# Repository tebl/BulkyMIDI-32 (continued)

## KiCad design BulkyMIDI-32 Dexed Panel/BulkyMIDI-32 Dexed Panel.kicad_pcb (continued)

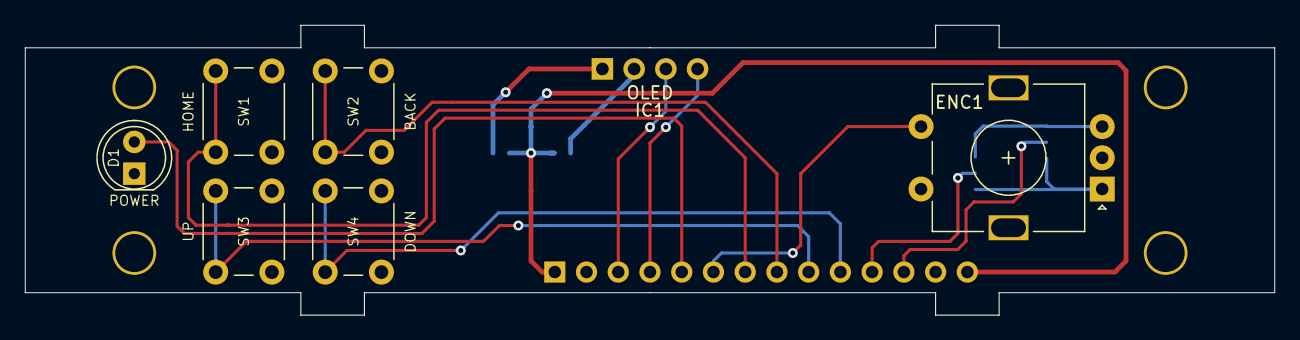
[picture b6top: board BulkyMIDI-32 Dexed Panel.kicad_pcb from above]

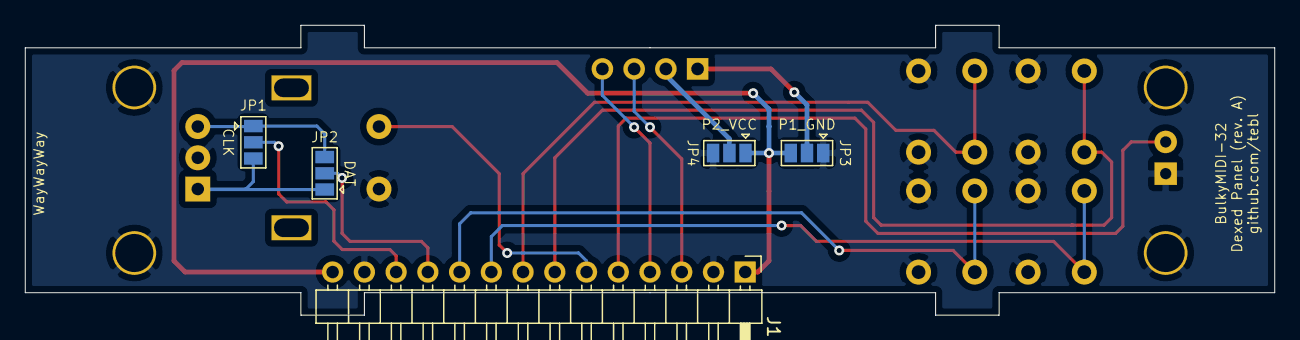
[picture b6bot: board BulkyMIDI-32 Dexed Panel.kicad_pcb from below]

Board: 2 copper layers, 100.0 x 23.2 mm, 16 parts (5 on the bottom side), 16 nets.

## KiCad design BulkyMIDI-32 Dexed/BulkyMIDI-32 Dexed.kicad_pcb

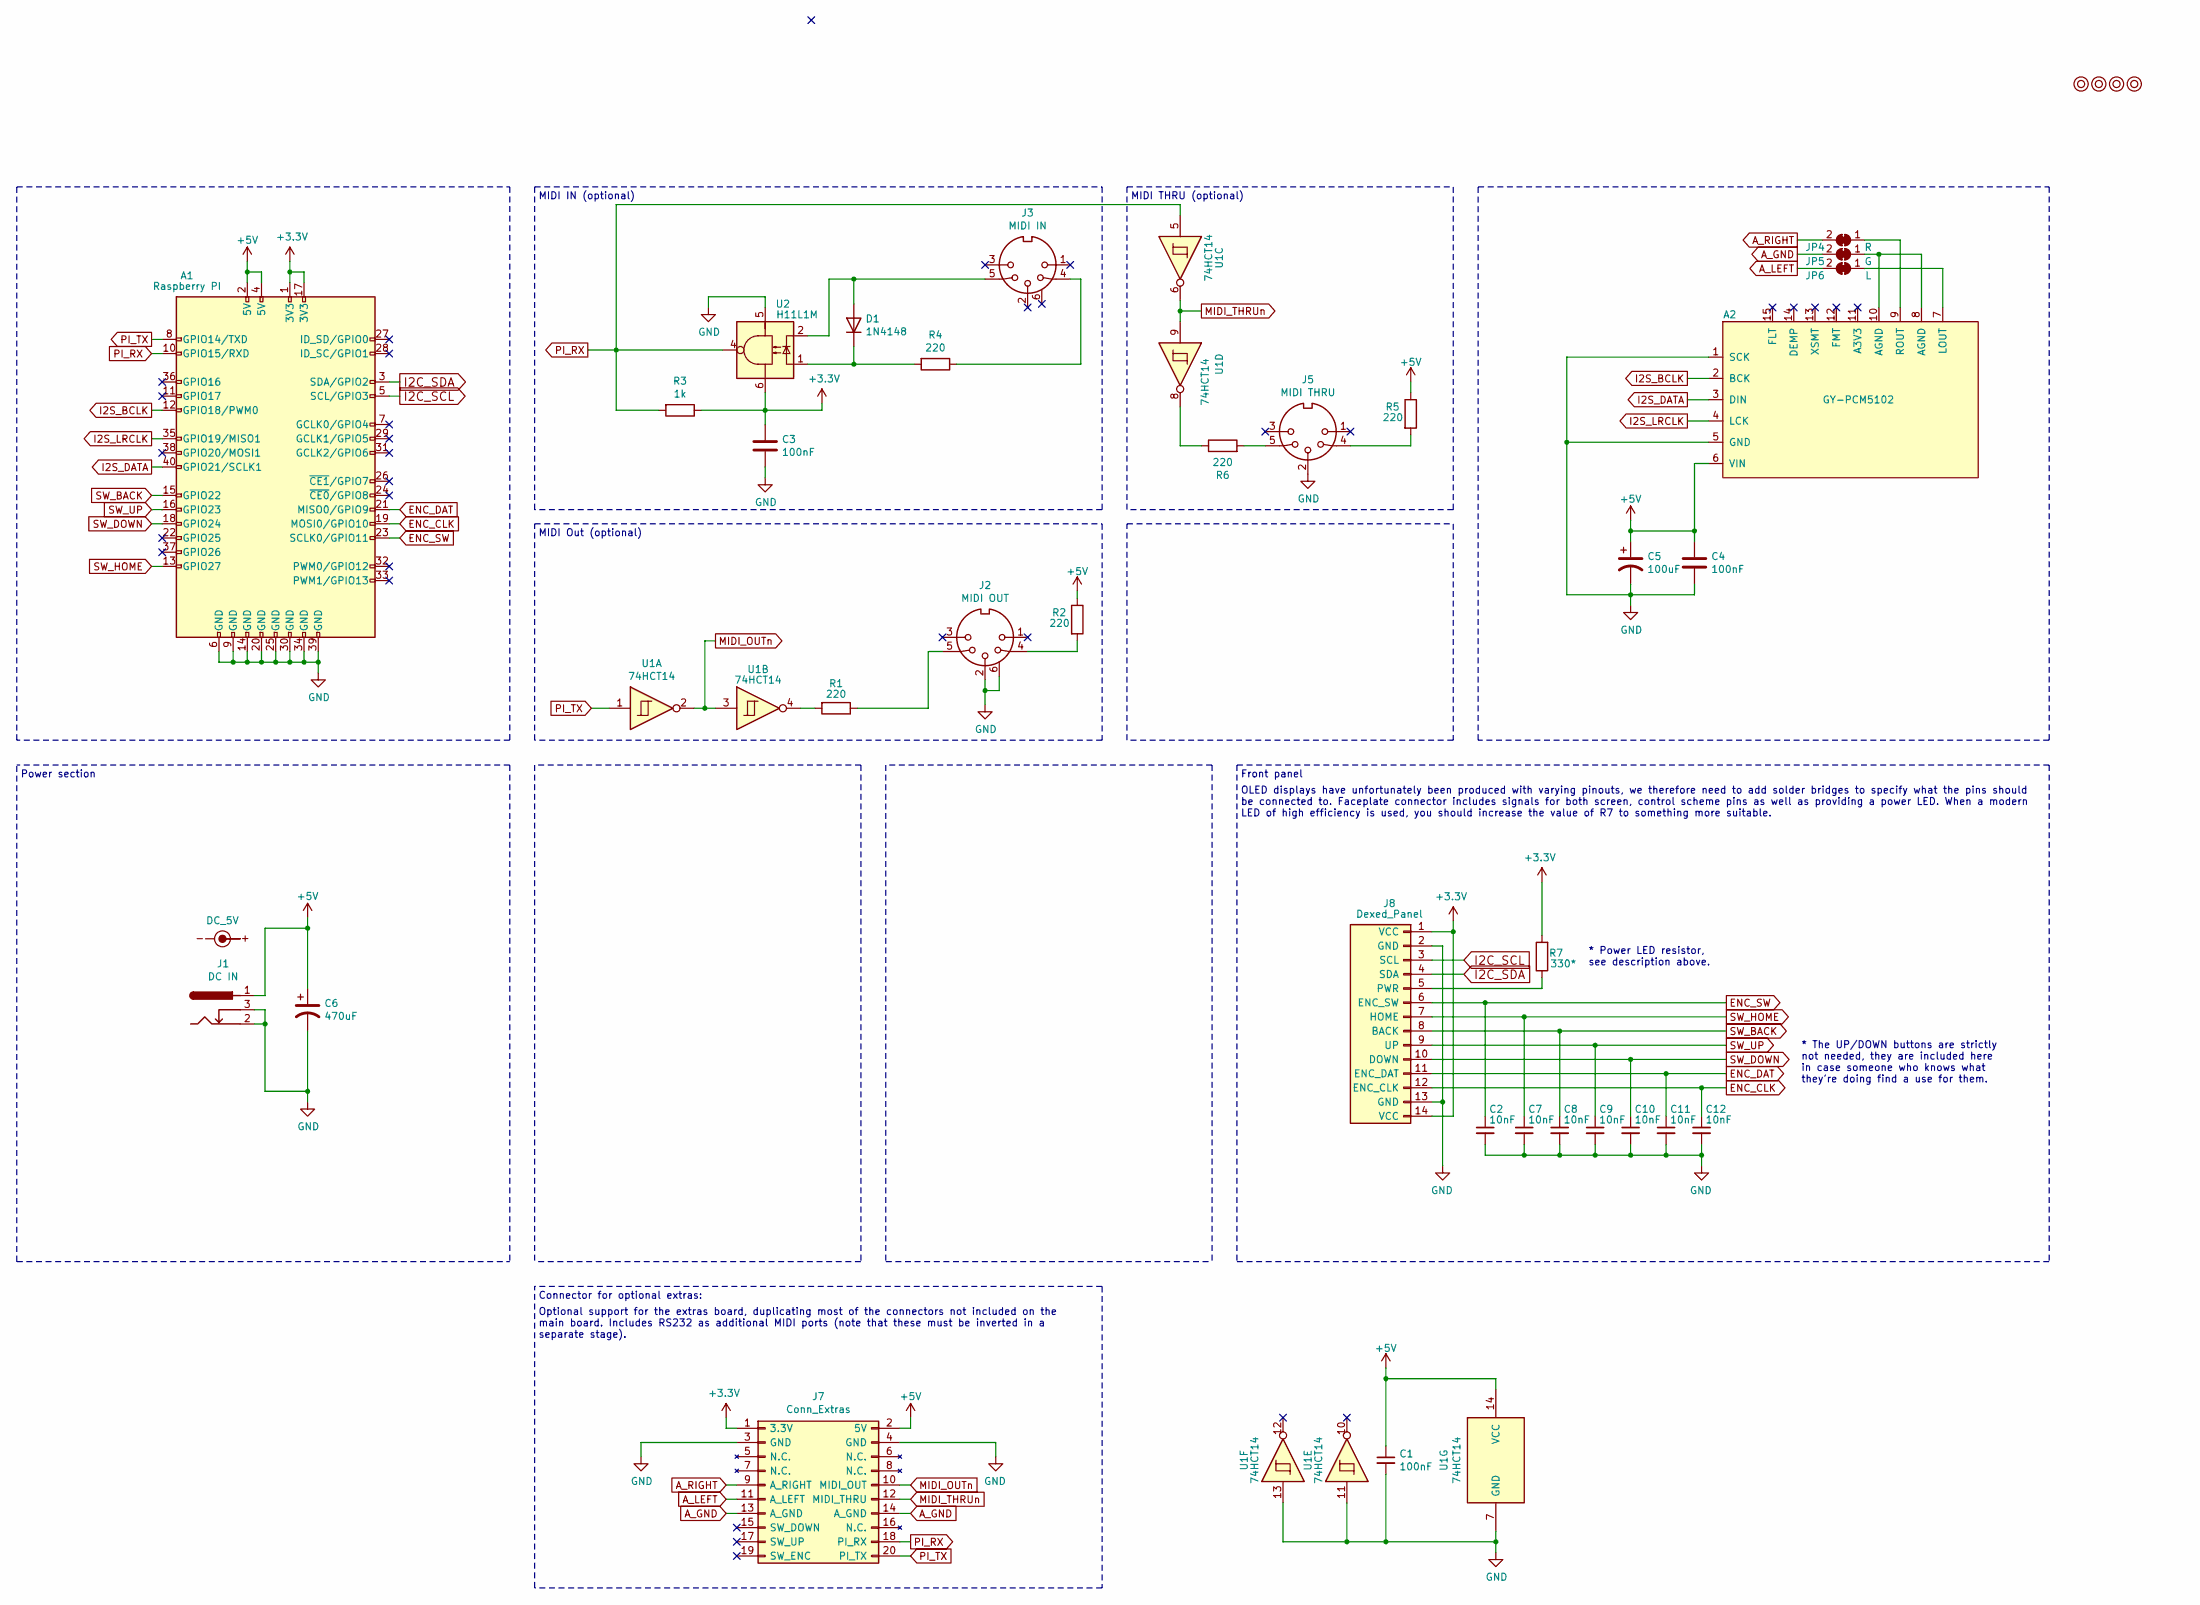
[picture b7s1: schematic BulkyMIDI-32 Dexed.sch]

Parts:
A1: Raspberry PI; Raspberry_Pi_3B_Socketed_THT_FaceDown_MountingHoles
A2: GY-PCM5102
C1, C3, C4: 100nF; C_Rect_L7.0mm_W2.0mm_P5.00mm
C2, C7, C8, C9, C10, C11, C12: 10nF; C_Rect_L7.0mm_W2.0mm_P5.00mm
C5: 100uF; CP_Radial_D6.3mm_P2.50mm
C6: 470uF; CP_Radial_D8.0mm_P3.50mm
D1: 1N4148; D_DO-35_SOD27_P7.62mm_Horizontal
J1: DC IN; BARREL_JACK
J2: MIDI OUT; DIN5_MIDI_OUT
J3: MIDI IN; DIN5_MIDI_IN
J5: MIDI THRU; JST_XH_B5B-XH-A_1x05_P2.50mm_Vertical
J7: Conn_Extras; PinSocket_2x10_P2.54mm_Vertical
J8: Dexed_Panel
JP4: R; SolderJumper-2_P1.3mm_Open_TrianglePad1.0x1.5mm
JP5: G; SolderJumper-2_P1.3mm_Open_TrianglePad1.0x1.5mm
JP6: L; SolderJumper-2_P1.3mm_Open_TrianglePad1.0x1.5mm
M1, M2, M3, M4: Mounting; M3
R1, R2, R4, R5, R6: 220; R_Axial_DIN0207_L6.3mm_D2.5mm_P10.16mm_Horizontal
R3: 1k; R_Axial_DIN0207_L6.3mm_D2.5mm_P10.16mm_Horizontal
R7: 330*; R_Axial_DIN0207_L6.3mm_D2.5mm_P10.16mm_Horizontal
SYM1: DC_5V; PWR_Specification
U1: 74HCT14; DIP-14_W7.62mm
U2: H11L1M; DIP-6_W7.62mm

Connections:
+3V3: A1.1 (3V3), A1.17 (3V3), C3.1, J7.1 (3.3V), J8.1 (VCC), J8.14 (VCC), R3.1, R7.2, U2.6
+5V: A1.2 (5V), A1.4 (5V), A2.6 (VIN), C1.1, C4.1, C5.1, C6.1, J1.1, J7.2 (5V), R2.1, R5.1, U1.14 (VCC)
A_GND: J7.13 (A_GND), J7.14 (A_GND), JP5.2 (B)
A_LEFT: J7.11 (A_LEFT), JP6.2 (B)
A_RIGHT: J7.9 (A_RIGHT), JP4.2 (B)
ENC_CLK: A1.19 (MOSI0/GPIO10), C12.1, J8.12 (ENC_CLK)
ENC_DAT: A1.21 (MISO0/GPIO9), C11.1, J8.11 (ENC_DAT)
ENC_SW: A1.23 (SCLK0/GPIO11), C2.1, J8.6 (ENC_SW)
GND: A1.6 (GND), A1.9 (GND), A1.14 (GND), A1.20 (GND), A1.25 (GND), A1.30 (GND), A1.34 (GND), A1.39 (GND), A2.1 (SCK), A2.5 (GND), C1.2, C2.2, C3.2, C4.2, C5.2, C6.2, C7.2, C8.2, C9.2, C10.2, C11.2, C12.2, J1.2, J1.3, J2.2, J2.6, J5.2, J7.3 (GND), J7.4 (GND), J8.2 (GND), J8.13 (GND), U1.7 (GND), U1.11, U1.13, U2.5
I2C_SCL: A1.5 (SCL/GPIO3), J8.3 (SCL)
I2C_SDA: A1.3 (SDA/GPIO2), J8.4 (SDA)
I2S_BCLK: A1.12 (GPIO18/PWM0), A2.2 (BCK)
I2S_DATA: A1.40 (GPIO21/SCLK1), A2.3 (DIN)
I2S_LRCLK: A1.35 (GPIO19/MISO1), A2.4 (LCK)
MIDI_OUTn: J7.10 (MIDI_OUT), U1.2, U1.3
MIDI_THRUn: J7.12 (MIDI_THRU), U1.6, U1.9
unnamed: A2.7 (LOUT), JP6.1 (A)
unnamed: A2.9 (ROUT), JP4.1 (A)
unnamed: A2.8 (AGND), A2.10 (AGND), JP5.1 (A)
unnamed: D1.1 (K), R4.2, U2.1
unnamed: D1.2 (A), J3.5, U2.2
unnamed: J2.4, R2.2
unnamed: J2.5, R1.1
unnamed: J3.4, R4.1
unnamed: J5.4, R5.2
unnamed: J5.5, R6.2
unnamed: J8.5 (PWR), R7.1
unnamed: R1.2, U1.4
unnamed: R6.1, U1.8
PI_RX: A1.10 (GPIO15/RXD), J7.18 (PI_RX), R3.2, U1.5, U2.4
PI_TX: A1.8 (GPIO14/TXD), J7.20 (PI_TX), U1.1
SW_BACK: A1.15 (GPIO22), C8.1, J8.8 (BACK)
SW_DOWN: A1.18 (GPIO24), C10.1, J8.10 (DOWN)
SW_HOME: A1.13 (GPIO27), C7.1, J8.7 (HOME)
SW_UP: A1.16 (GPIO23), C9.1, J8.9 (UP)

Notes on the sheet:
MIDI Out (optional)
MIDI THRU (optional)
MIDI IN (optional)
Power section
Front panel
OLED displays have unfortunately been produced with varying pinouts, we therefore need to add solder bridges to specify what the pins should be connected to. Faceplate connector includes signals for both screen, control scheme pins as well as providing a power LED. When a modern LED of high efficie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
Connector for optional extras:
Optional support for the extras board, duplicating most of the connectors not included on the main board. Includes RS232 as additional MIDI ports (note that these must be inverted in a separate stage).
* Power LED resistor, see description above.
* The UP/DOWN buttons are strictly not needed, they are included here in case someone who knows what they're doing find a use for them.

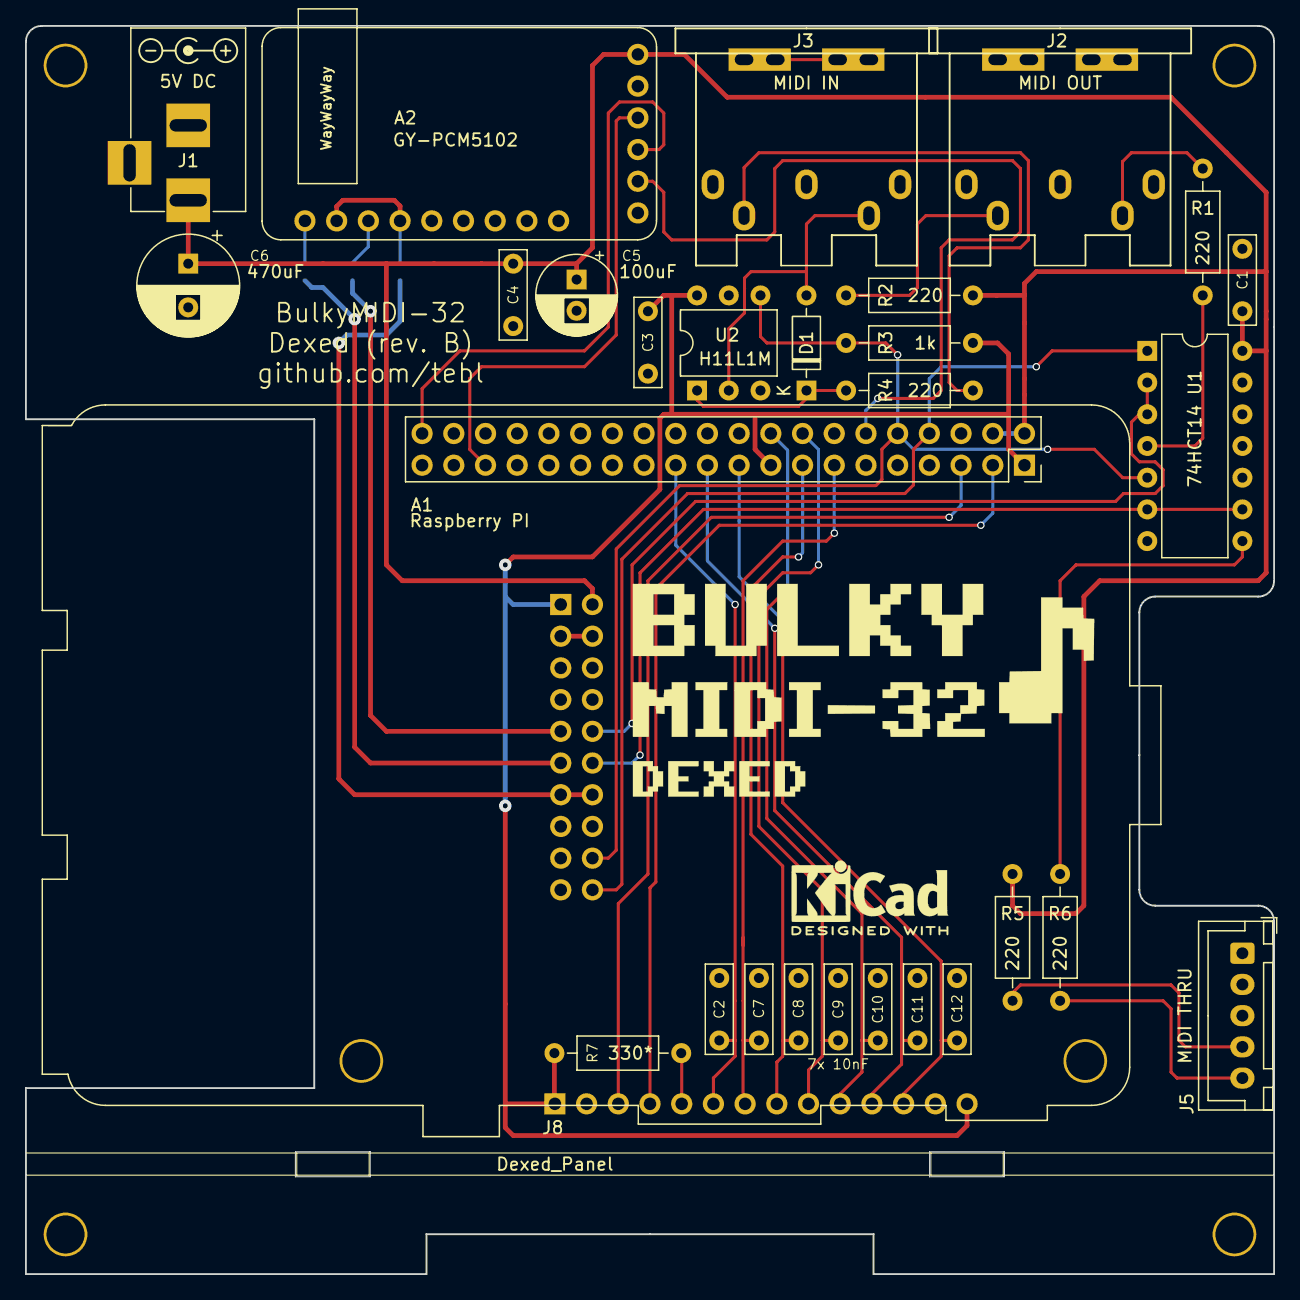
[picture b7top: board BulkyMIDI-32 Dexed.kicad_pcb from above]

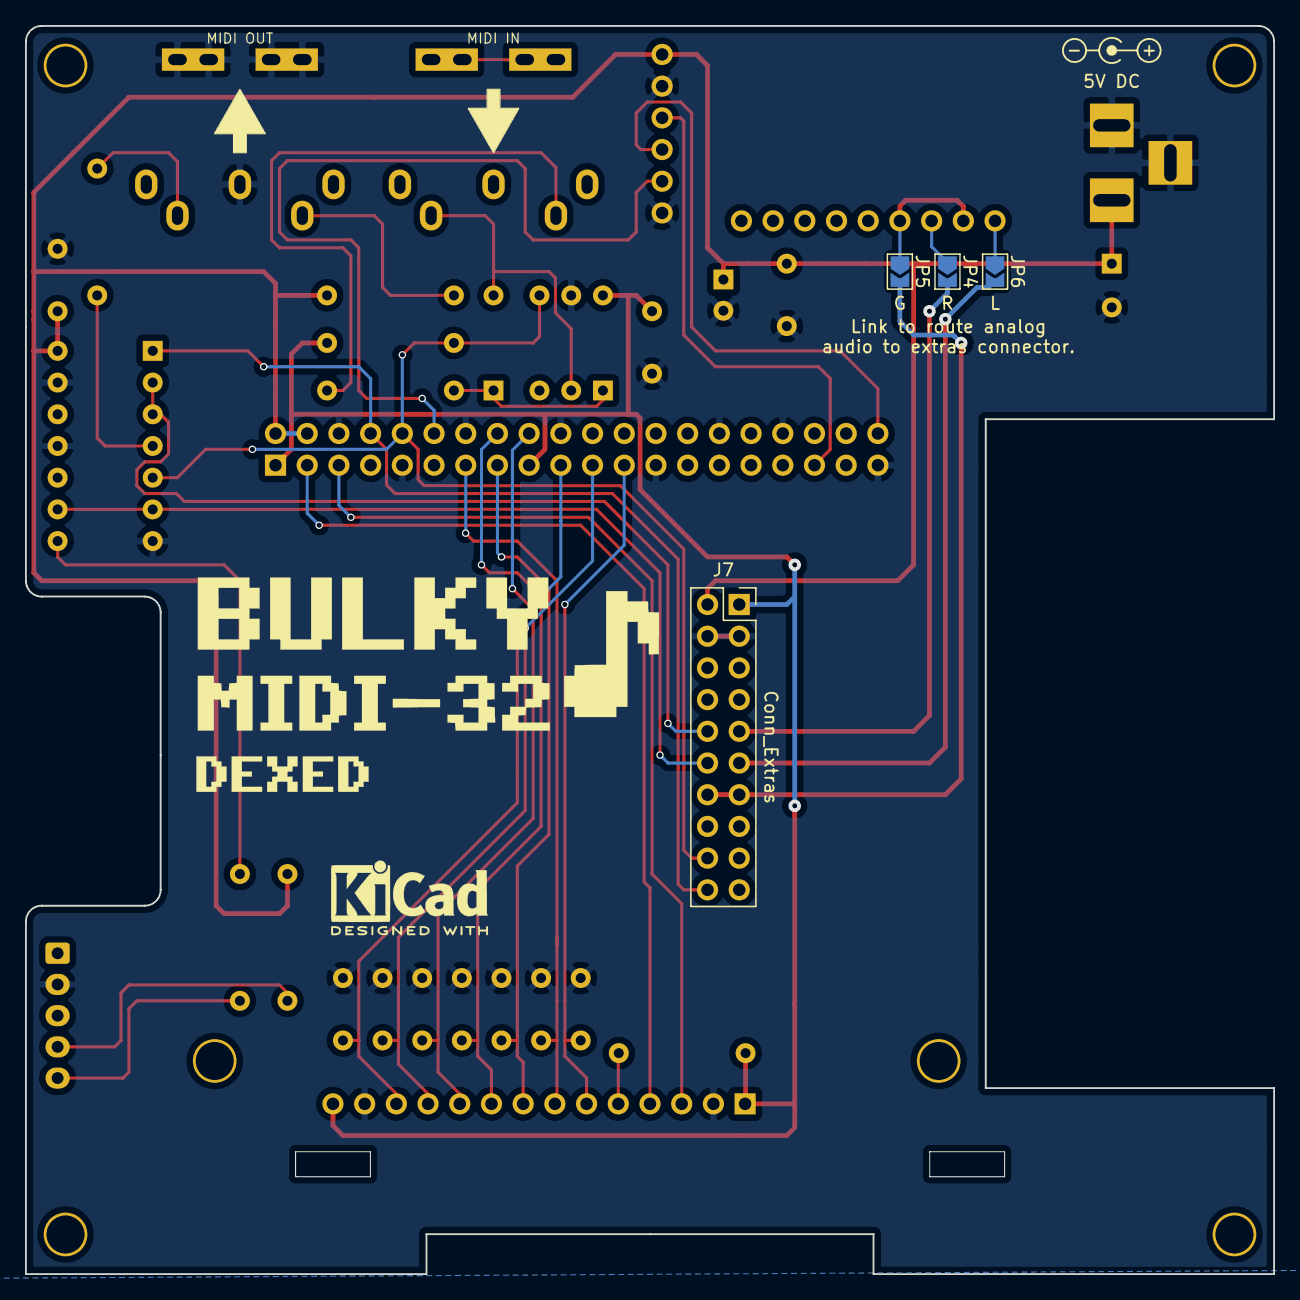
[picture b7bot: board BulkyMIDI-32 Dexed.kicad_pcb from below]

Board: 2 copper layers, 100.0 x 100.0 mm, 38 parts (4 on the bottom side), 35 nets.

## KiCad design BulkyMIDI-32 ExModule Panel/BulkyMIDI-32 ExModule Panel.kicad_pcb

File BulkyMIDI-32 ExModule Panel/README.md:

# BulkyMIDI-32 ExModule Panel
This is a front-facing panel for controlling the *BulkyMIDI-32 ExModule*, it is optional by design. I do however find that it makes the system a lot more enjoyable to use, mostly by looking significantly better while sitting on my desk. While it functionally replaces some of the components on the main module, the components themselves are different - this document therefore have its own [BOM](#3-bom) at the bottom of this document. Keep this in mind when ordering parts.

- [1> Building the device](#1-building-the-device)
  - [1.1> Soldering it together](#11-soldering-it-together)
- [2> Schematic](#2-schematic)
- [3> BOM](#3-bom)

# 1> Building the device
Building a device such as this assumes you have at least minor experience soldering things together, recommended is that you at the very least have access to a soldering station with adjustable temperature. If currently available, you should probably start with 60/40 rosin core solder as the lead-free alternatives tends to be a bit harder to work with.

With requirements for basic equipment sorted, we need to talk a bit about what you want to achieve while building this project. The reason I ask is that while you can build a functional *ExModule* using the main module by itself, you can also build the complete version of the unit - that would include front panel as well as two faceplates, one goes on the top and the other for the front. 

Now that you know what you want to build, we can get started on the most expensive step in any build process - shopping! So, head on over to the [BOM](#3-bom)-section for some information on what kind of components that you'll need. While I would have liked to give you specific part numbers for "reputable" electronic part suppliers, I generally can't afford to shop there. For that reason I usually make due with what I can find on such sites as ebay, AliExpress and any similar sites that commonly sell cheap Chinese components. The downside to this is that I won't be able to link to a part directly and expect it to be there two days for now, so you'll need to consider the description listed as *mere* suggestions of what to search for. The one you'll need will usually be the more common of the responses as I try to keep away from the more exotic options.

## 1.1> Soldering it together

The construction of this unit should be fairly straight-forward, just take your time in order to make sure everything goes into place - more or less straight. I usually recommend starting by having a good look at the PCBs, try to figure out where all of the listed components go and in which orientation they go in (all of this should be clearly marked on the silkscreen). 

The first component to install might be a bit backwards to normal convention, but I've started wth the 8mm hex standoffs. The hex shape needs to be rotated a flat edge lines up with the left and right edges of the PCB, the reason for this will become evident when we attempt to install it onto the main module. As these are just nylon, I've made things slightly easier for myself by using a sharp knife to trim a bit off the vertical edges of them - in particular the one sitting just above the power LED.

As for the next step, I've skipped a bit too far ahead and simply added just about everything. I started with the right-angle pin headers, paying attention to the fact that they will be on the flipside of the PCB as compared to the other components. In order for the alignment of the remaining components to be perfectly straight, my recommendation is to just insert them into place the holes where they go - then mount the [front plate](https://github.com/tebl/BulkyMIDI-32/tree/main/faceplates/BulkyMIDI-32%20ExModule%20FP1) on the top of it.

The only real stumbling block is getting the LED, the right way around. On some LEDs it's easy to see that there is a flat side to the bottom of it, on some it's not quite so easy to see this - so when in doubt, make sure to put the shorter leg of the LED into the hole with a square pad. Once you are ready to start soldering in the remaining components, a single pin of each component should then soldered - check the alignment, reheat and adjust if needed. I prefer to push the LED slightly from the back to ensure that it ends up sitting flush against the front plate (take care not to put your finger on the pin that you are heating up).

The completed unit is shown above, except that I am temporarily using some standoffs as the outer screws holding the faceplate onto the panel. You can use standard screws if you want to, I'm just using them during assembly as they are easier to remove by hand. For the installation of the panel it should mostly just slide into place, but all of that should be covered by the documentation for the [main](https://github.com/tebl/BulkyMIDI-32/tree/main/BulkyMIDI-32%20ExModule)-module.

**NB!** If you find that the panel doesn't quite slide into place, check that the standoffs on both the panel and main module have been rotated as described. Looking at the orientation of the pictures shown in this document, this means that both of them should have standoffs that have a flat side towards the left and right side of the PCBs.

# 2> Schematic
The supplied KiCad files should be sufficient as both a schematic and as a  starting point for ordering PCBs (basically you could just zip the contents of the export folder and upload that on a fabrication site), the schematic is also available in [PDF-format](https://github.com/tebl/BulkyMIDI-32/tree/main/documentation/schematic) and this is what you'll need to print and work your way through this things don't work as expected after assembly.

# 3> BOM
Most parts should be easy to get a hold of from your favourite local electronic component shop, but given that I don't have access to such shops where I live so everything was based on whatever I could get cheapest from eBay/AliExpress (free shipping, but plan on waiting 3-4 weeks for delivery). Components in parenthesis can be considered optional for features beyond the more basic functionality, but where's the fun in that? You deserve the complete package.

| Reference             | Item                                                              | Count | Order  |
| --------------------- | ----------------------------------------------------------------- | ----- | ------ |
| Panel PCB             | Fabricate using Gerber files                                      |     1 | [PCBWay](https://www.pcbway.com/project/shareproject/BulkyMIDI_32_ExModule_Panel_8050038f.html)
| D1,D2                 | 5mm LEDs, preferably diffused and not the bright clear ones)      |     2 |
| J1                    | Standard right-angle pin header (2.54mm spacing)                  |     1 |
| SW1                   | 6x6x12mm momentary button                                         |     1 |
| Mounting ****         | Nylon M3 hex standoffs 8mm (M-F)                                  |     4 |
| Mounting ****         | Nylon M3x6mm nylon screws                                         |     4 |
| Mounting ****         | Nylon M3x6mm nylon nuts                                           |     4 |

****) These are available in the form of kits usually advertised *M3 nylon standoff kit* which should contain most of what you'd need. I do however recommend that you pick up extra M-F standoffs of lengths 8mm and 20mm, as quite a lot of them will be used when building more than one module.

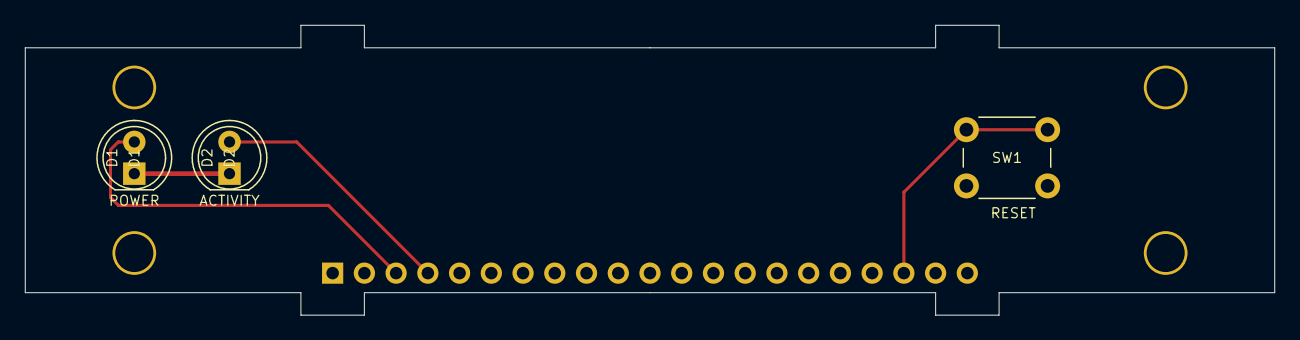
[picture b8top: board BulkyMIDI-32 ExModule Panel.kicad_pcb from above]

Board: 2 copper layers, 100.0 x 23.2 mm, 8 parts (1 on the bottom side), 4 nets.

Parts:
D1: POWER; LED_D5.0mm
D2: ACTIVITY; LED_D5.0mm
J1: ExModule; PinHeader_1x21_P2.54mm_Horizontal
M1, M2, M3, M4: Mounting_Pin; M3_pin
SW1: RESET; SW_PUSH_6mm

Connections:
/ACT: D2.2, J1.4
/PWR: D1.2, J1.3
/RESET: J1.19, SW1.1
GND: D1.1, D2.1, J1.2, J1.20, M1.1, M2.1, M3.1, M4.1, SW1.2
